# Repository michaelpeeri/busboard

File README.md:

# busboard - bus breakout board for Arduino pro-mini
Created to allow easy prototyping of battery-powered remote sensing projects.
Designed to fit genuine (Sparkfun) boards, or most common clones.
Created using KiCad.

Features:
* SPI bus broken out for 2 devices, with optional nRF24 connector also on the bus (connected through jumpers). Default SS pin (D10) connected to nRF24 CS/SS.
* I2C/TWI bus broken out for 3 devices (with pull-up resistors).
* 4 analog pins broken out with separate ground plane.
* Digital pins broken out (but note - using non-standard pin pitch).
* 5cm x 5cm form factor; mounting holes for 3 M3 stand-offs with 4cm pitch, connected to ground plane to support shielding (but note nRF24 antenna must remain outside shielding).

# Power
Optional connector for Pololu drop-down regulators (4-pin). Battery connected through switch and a resistor divider for battery voltage measurement (on pin A7).
SHDN pin connected (through jumper) to D7 (but can be left floating on these devices).
If another regulator is used (including the built-in regulator), solder a jumper wire from RAW pin on Pololu connector to RAW pin on the pro-mini.

# Analog pins
* A0-A3 - broken out to analog section (with a separate ground plane connected at a star point)
* A6 - available but not broken out
* A7 - connected to battery (through resistor divider)
* A4-A5 are shared with I2C on Pro-minis.

# nRF24 connector (with 3.3v Pro-minis)
SPI pins (MOSI/MISO/SCLK) connected through solder jumpers (to reduce EMI when not used).
SS connected (through jumper) to D10.
IRQ connected (through jumper) to D3.
CE/EN connected (through jumper) to D8.

# RX/TX
Broken out.

# FTDI header
Not broken out (should be available directly on Pro-mini board depending on the headers used).

# TODO (in next revision)
* Add jumper to bypass DC-DC converter module and connent batt. RAW to board RAW.
* Add second power switch footprint (for a 2.54mm-pitch switch)
* Move the power switch footprint closer to the edge of the board
* Change power switch footprint to have slightly larger diameter outer mounting holes
* Increase the width of the traces of the RAW network (the existing width should be more than sufficient for the low currents used, but why not?)
* Add github URL and OSH logo

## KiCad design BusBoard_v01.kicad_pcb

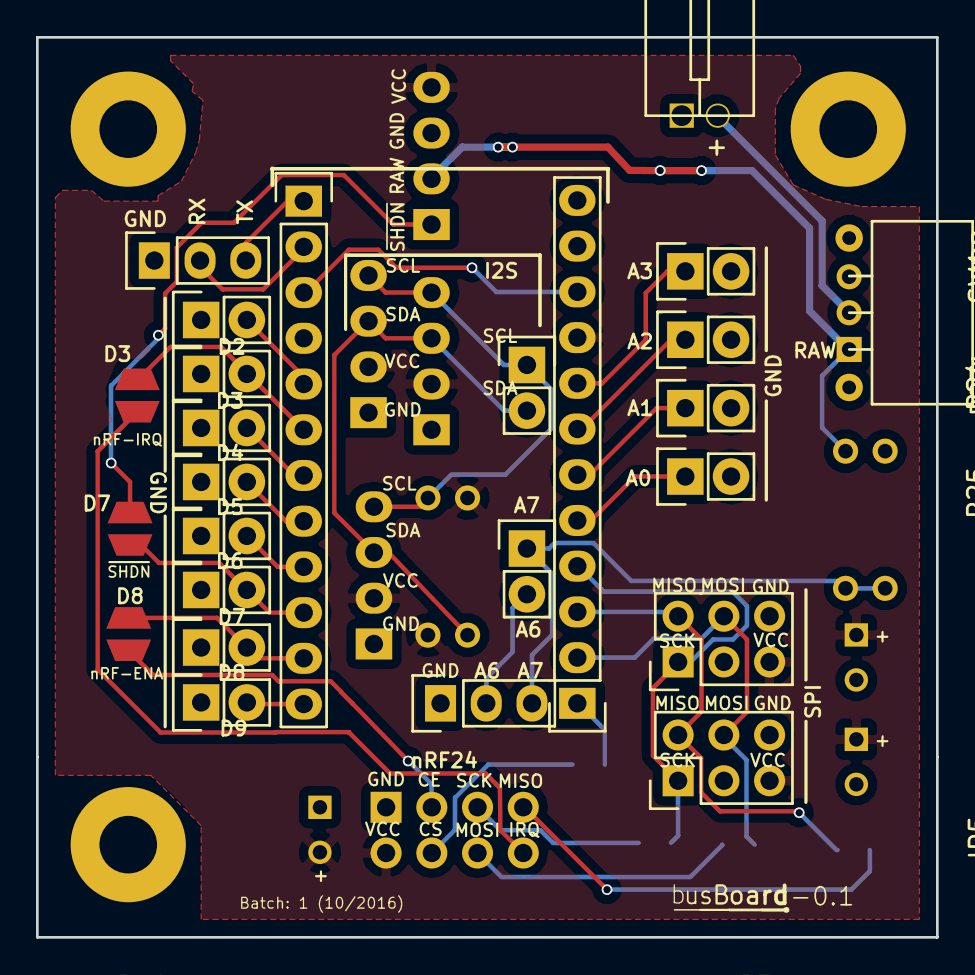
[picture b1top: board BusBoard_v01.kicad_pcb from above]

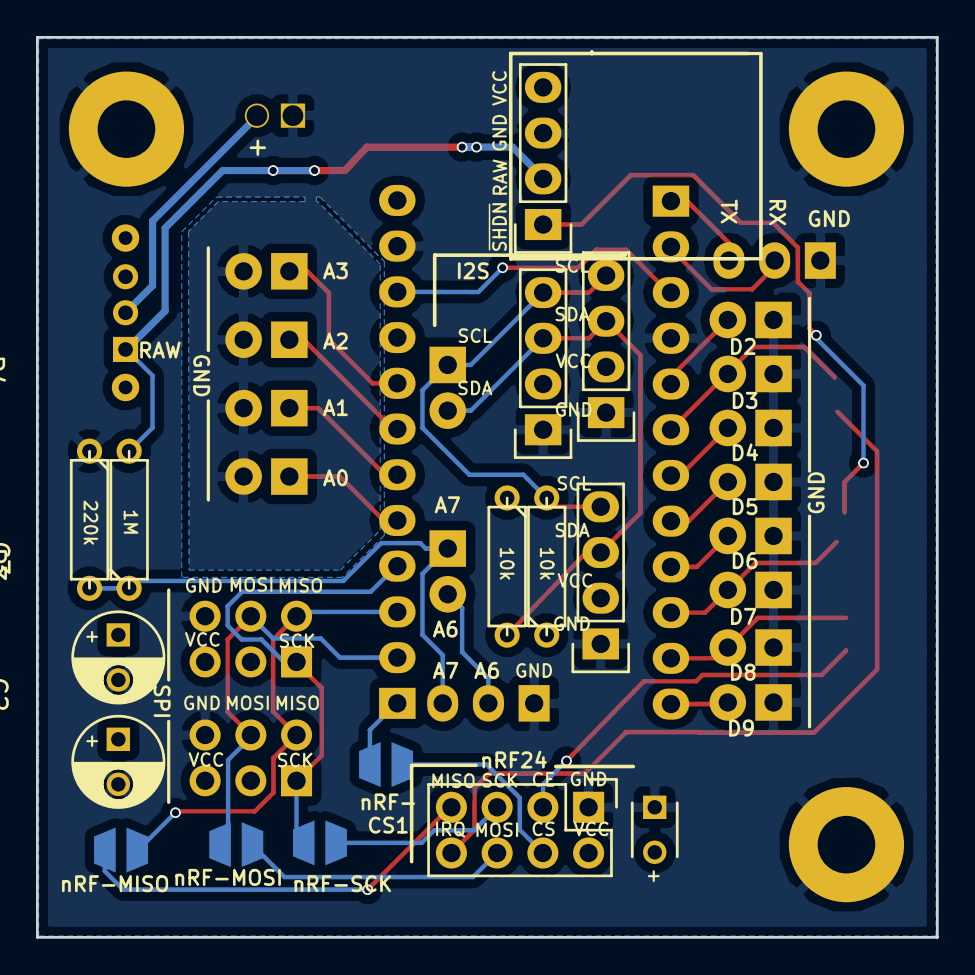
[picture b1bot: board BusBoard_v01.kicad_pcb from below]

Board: 2 copper layers, 50.0 x 50.0 mm, 41 parts (15 on the bottom side), 34 nets.

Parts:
C1: C_Small; C_Disc_D3_P2.5
C2, C3: CP_Small; C_Radial_D5_L6_P2.5
JP1, JP2, JP3, JP4, JP5, JP6, JP7: JUMPER; Small_jumper
P1: CONN_02X04; Pin_Header_Straight_2x04
P2, P7: CONN_01X12; Pin_Header_Straight_1x12
P3, P6: CONN_01X03; Pin_Header_Straight_1x03
P4, P5, P8, P9, P10, P11, P12, P13, P14, P15, P22, P23, P24, P25: CONN_01X02; Pin_Header_Straight_1x02
P16, P17: CONN_02X03; Pin_Header_Straight_2x03
P26, P33, P34, P35: CONN_01X04; Pin_Header_Straight_1x04
P27: CONN_01X02_BATT; JWT_Vertical_A3963-RM3.96mm-2
R1, R2: 10K; R3
R3, R4: R_Small; R3
SW1: Switch_SPDT_x2; SW_Micro_SPST_Angled_5holes

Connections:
A0: P7.5, P25.1
A1: P7.6, P24.1
A2: P7.7, P23.1
A3: P7.8, P22.1
A6: P4.2, P6.2
A7: P4.1, P6.3, R3.1, R4.2
D2: P2.5, P10.2
D3: JP4.1, P2.6, P11.2
D4: P2.7, P12.2
D5: P2.8, P13.2
D6: P2.9, P14.2
D7: JP3.2, P2.10, P15.2
D8: JP1.1, P2.11, P9.2
D9: P2.12, P8.2
GND: C1.1, C2.2, C3.2, P1.1, P2.4, P3.1, P6.1, P7.11, P8.1, P9.1, P10.1, P11.1, P12.1, P13.1, P14.1, P15.1, P16.6, P17.6, P22.2, P23.2, P24.2, P25.2, P26.3, P27.1, P33.1, P34.1, P35.1, R4.1
I2C_SCL_A5: P5.1, P33.4, P34.4, P35.4, R1.2
I2C_SDA_A4: P5.2, P33.3, P34.3, P35.3, R2.2
unnamed: JP1.2, P1.3
unnamed: JP2.2, P1.4
unnamed: JP3.1, P26.1
unnamed: JP4.2, P1.8
unnamed: JP5.2, P1.7
unnamed: JP6.2, P1.5
unnamed: JP7.2, P1.6
unnamed: P27.2, SW1.2
RAW: P26.2, R3.2, SW1.1
RST: P2.3, P7.10
RX: P2.2, P3.2
SPI_MISO: JP5.1, P7.3, P16.2, P17.2
SPI_MOSI: JP7.1, P7.2, P16.4, P17.4
SPI_SCK: JP6.1, P7.4, P16.1, P17.1
SPI_SS1: JP2.1, P7.1
TX: P2.1, P3.3
VCC: C1.2, C2.1, C3.1, P1.2, P7.9, P16.5, P17.5, P26.4, P33.2, P34.2, P35.2, R1.1, R2.1

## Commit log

2016-10-05 Initial commit (final checks before initial fab)
2016-10-05 Initial commit of custom footprints
